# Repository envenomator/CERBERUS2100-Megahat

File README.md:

# Cerberus 2100 hat for the Arduino MEGA

Pinout table can be found in the silkscreen on the PCB

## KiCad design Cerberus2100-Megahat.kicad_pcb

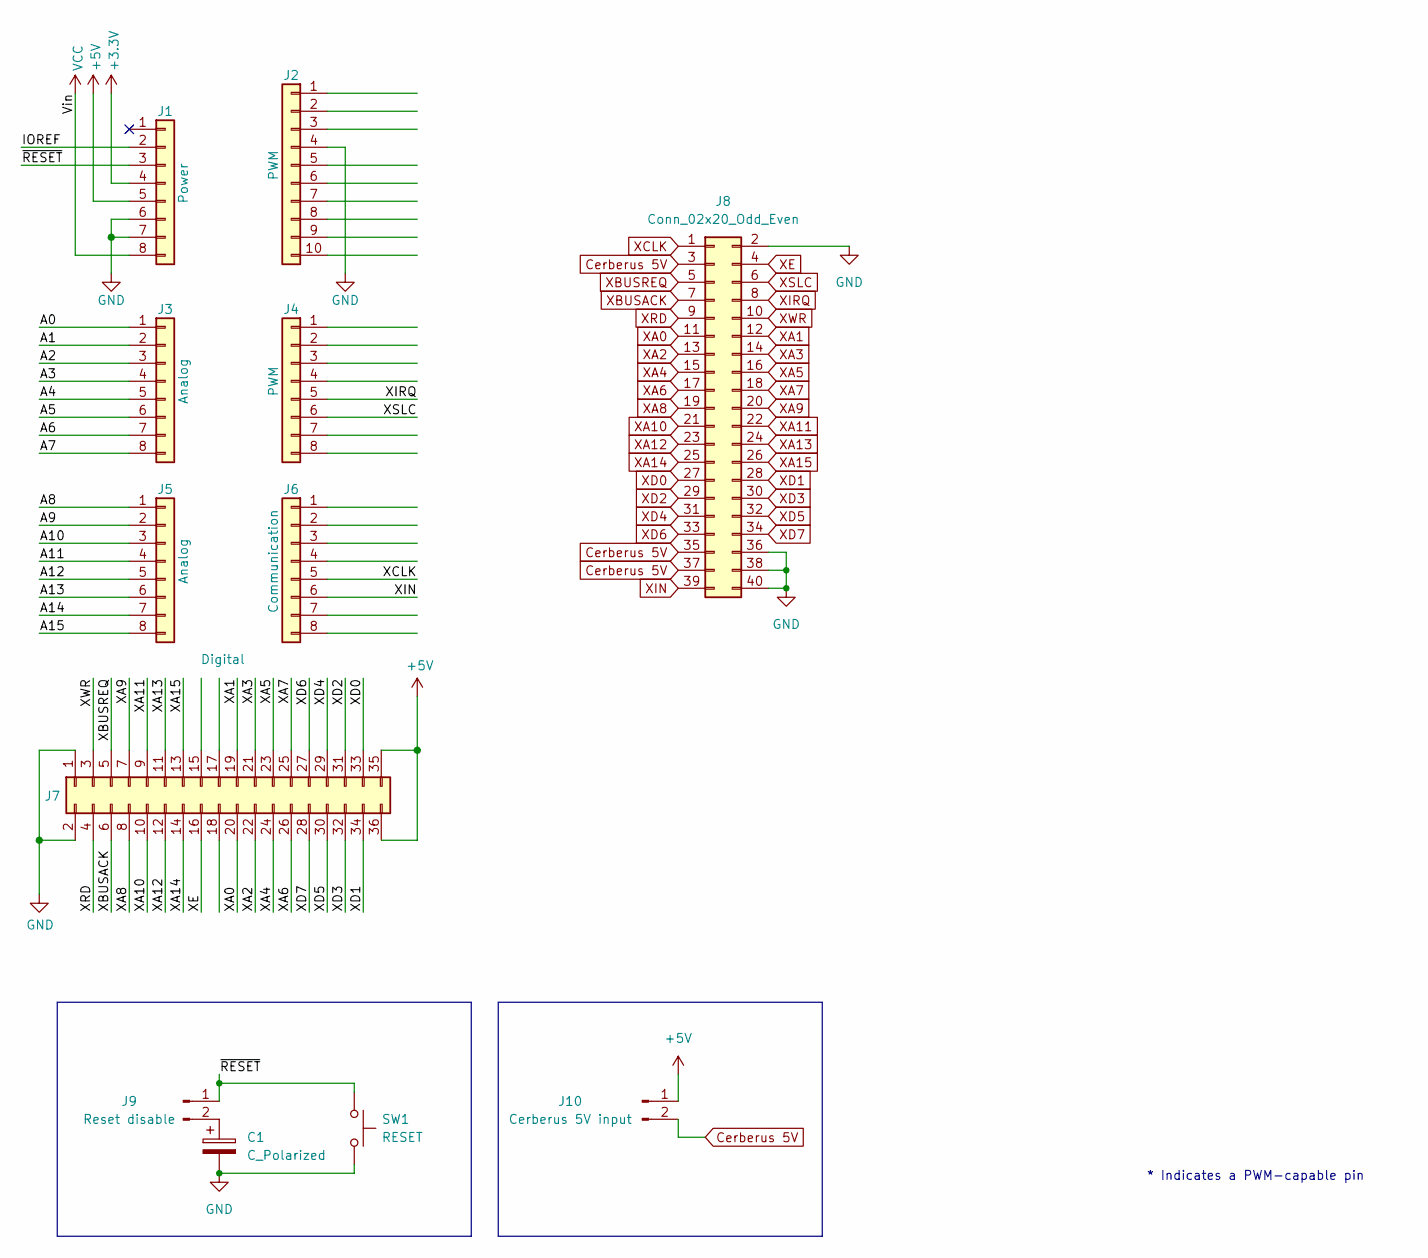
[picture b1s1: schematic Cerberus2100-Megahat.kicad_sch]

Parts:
C1: C_Polarized; CP_Radial_D5.0mm_P2.50mm
J1: Power; PinSocket_1x08_P2.54mm_Vertical
J2: PWM; PinSocket_1x10_P2.54mm_Vertical
J3, J5: Analog; PinSocket_1x08_P2.54mm_Vertical
J4: PWM; PinSocket_1x08_P2.54mm_Vertical
J6: Communication; PinSocket_1x08_P2.54mm_Vertical
J7: Digital; PinSocket_2x18_P2.54mm_Vertical
J8: Conn_02x20_Odd_Even; IDC-Header_2x20_P2.54mm_Vertical
J9: Reset disable; PinHeader_1x02_P2.54mm_Vertical
J10: Cerberus 5V input; PinHeader_1x02_P2.54mm_Vertical
SW1: RESET; SW_PUSH_6mm_H4.3mm

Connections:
+3V3: J1.4
+5V: J1.5, J7.35, J7.36, J10.1
/A0: J3.1
/A1: J3.2
/A2: J3.3
/A3: J3.4
/A4: J3.5
/A5: J3.6
/A6: J3.7
/A7: J3.8
/A8: J5.1
/A9: J5.2
/A10: J5.3
/A11: J5.4
/A12: J5.5
/A13: J5.6
/A14: J5.7
/A15: J5.8
/IOREF: J1.2
/~RESET: J1.3, J9.1, SW1.1
Cerberus 5V: J8.3, J8.35, J8.37, J10.2
GND: C1.2, J1.6, J1.7, J2.4, J7.1, J7.2, J8.2, J8.36, J8.38, J8.40, SW1.2
unnamed: C1.1, J9.2
VCC: J1.8
XA0: J7.20, J8.11
XA1: J7.19, J8.12
XA2: J7.22, J8.13
XA3: J7.21, J8.14
XA4: J7.24, J8.15
XA5: J7.23, J8.16
XA6: J7.26, J8.17
XA7: J7.25, J8.18
XA8: J7.8, J8.19
XA9: J7.7, J8.20
XA10: J7.10, J8.21
XA11: J7.9, J8.22
XA12: J7.12, J8.23
XA13: J7.11, J8.24
XA14: J7.14, J8.25
XA15: J7.13, J8.26
XBUSACK: J7.6, J8.7
XBUSREQ: J7.5, J8.5
XCLK: J6.5, J8.1
XD0: J7.33, J8.27
XD1: J7.34, J8.28
XD2: J7.31, J8.29
XD3: J7.32, J8.30
XD4: J7.29, J8.31
XD5: J7.30, J8.32
XD6: J7.27, J8.33
XD7: J7.28, J8.34
XE: J7.16, J8.4
XIN: J6.6, J8.39
XIRQ: J4.5, J8.8
XRD: J7.4, J8.9
XSLC: J4.6, J8.6
XWR: J7.3, J8.10

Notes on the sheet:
* Indicates a PWM-capable pin

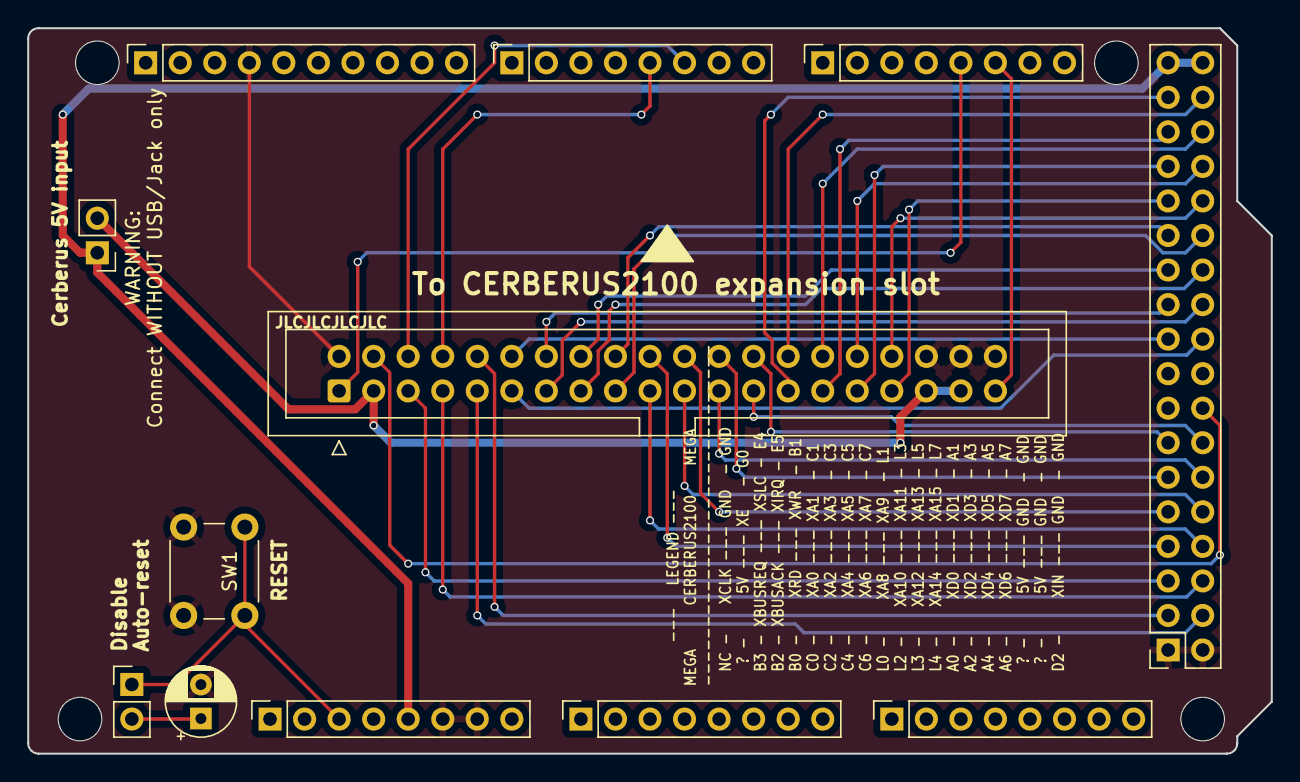
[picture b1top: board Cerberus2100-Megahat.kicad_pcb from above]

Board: 2 copper layers, 91.4 x 53.3 mm, 16 parts (0 on the bottom side), 38 nets.

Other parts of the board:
MH1, MH2, MH5, MH6: MountingHole_3.2mm

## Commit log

2023-08-31 JLCPCB order v1
2024-02-09 Picture and Schema in PDF added
